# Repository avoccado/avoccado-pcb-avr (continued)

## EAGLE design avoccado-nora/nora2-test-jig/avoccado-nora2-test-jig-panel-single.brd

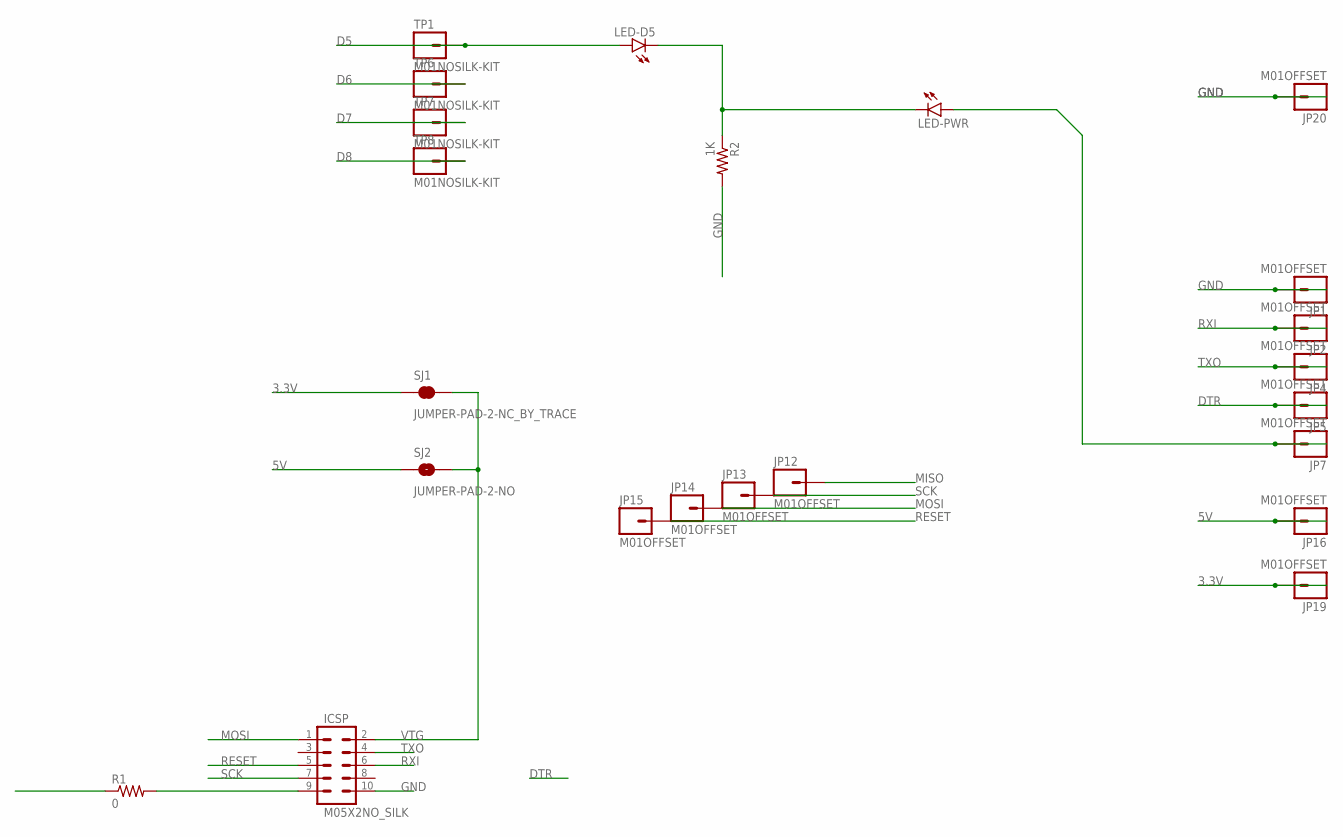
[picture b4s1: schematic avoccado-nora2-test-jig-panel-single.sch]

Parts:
ICSP: M05X2NO_SILK; 2X5_NOSILK
JP1, JP2, JP4, JP5, JP7, JP12, JP13, JP14, JP15, JP16, JP19, JP20: M01OFFSET; 1X01_OFFSET
LED-D5: LED0603; LED-0603
LED-PWR: LED0603; LED-0603
R1: 0; 1206
R2: 1K; 0603-RES
SJ1: JUMPER-PAD-2-NC_BY_TRACE; PAD-JUMPER-2-NC_BY_TRACE_YES_SILK
SJ2: JUMPER-PAD-2-NO; PAD-JUMPER-2-NO_NO_SILK
TP1, TP6, TP7, TP8: M01NOSILK-KIT; 1X01NS-KIT

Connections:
3.3V: JP19.1, SJ1.1
5V: JP16.1, SJ2.1
D5: LED-D5.A, TP1.1
D6: TP6.1
D7: TP7.1
D8: TP8.1
DTR: JP5.1
GND: ICSP.10, JP1.1, JP20.1, R2.2
MISO: JP12.1, R1.1
MISO1: ICSP.9, R1.2
MOSI: ICSP.1, JP14.1
unnamed: LED-D5.C, LED-PWR.C, R2.1
unnamed: JP7.1, LED-PWR.A
RESET: ICSP.5, JP15.1
RXI: ICSP.6, JP2.1
SCK: ICSP.7, JP13.1
TXO: ICSP.4, JP4.1
VTG: ICSP.2, SJ1.2, SJ2.2

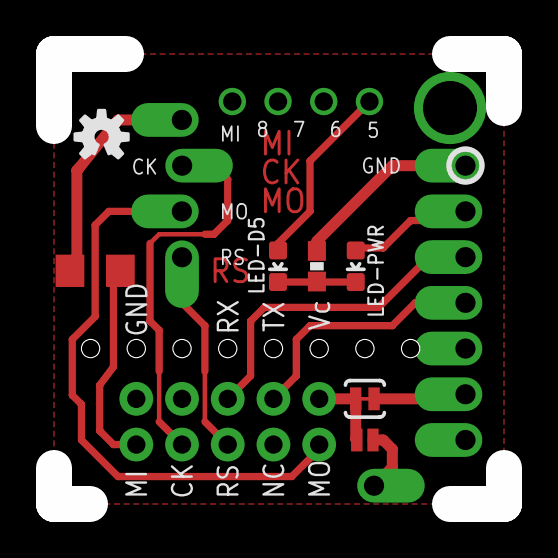
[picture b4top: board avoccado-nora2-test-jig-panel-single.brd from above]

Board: 2 copper layers, 25.0 x 25.0 mm, 24 parts (1 on the bottom side), 14 nets.

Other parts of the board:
LOGO2: OSHW-LOGOS; OSHW-LOGO-S

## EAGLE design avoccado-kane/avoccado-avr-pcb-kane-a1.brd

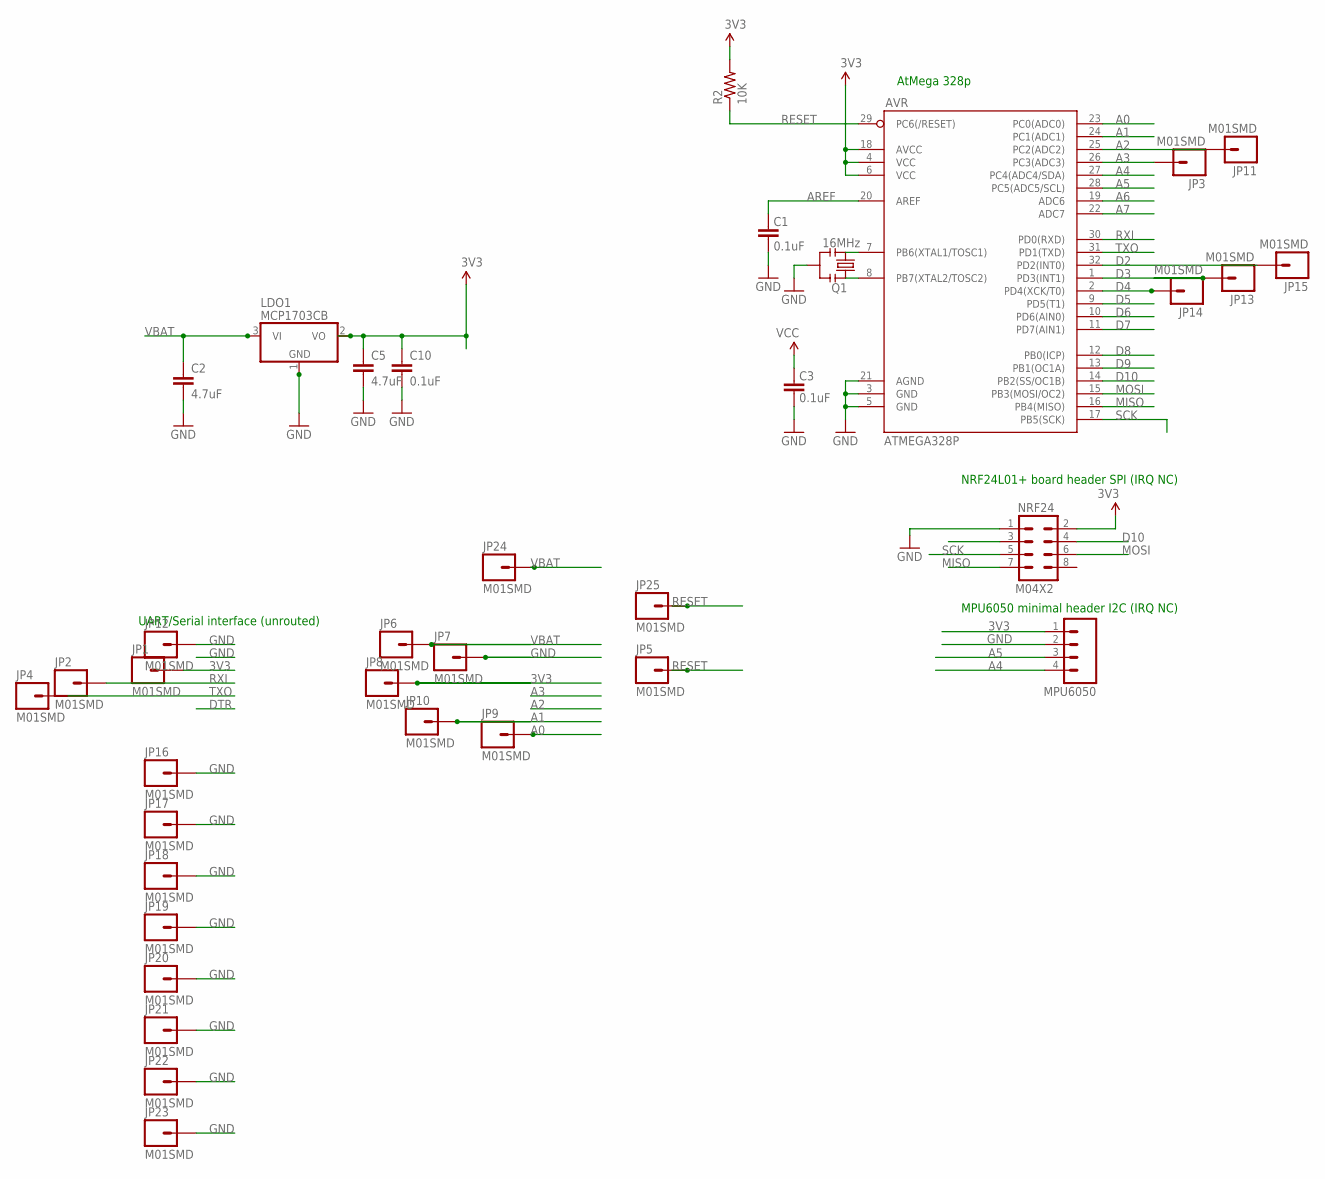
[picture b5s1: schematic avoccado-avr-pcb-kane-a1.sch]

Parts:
AVR: ATMEGA328P; TQFP32-08
C1, C3, C10: 0.1uF; C0402
C2, C5: 4.7uF; 0603-CAP
JP1, JP2, JP3, JP4, JP5, JP6, JP7, JP8, JP9, JP10, JP11, JP12, JP13, JP14, JP15, JP16, JP17, JP18, JP19, JP20, JP21, JP22, JP23, JP24, JP25: M01SMD; LUXEON-PAD
LDO1: MCP1703CB; SOT23
MPU6050: M041X04_NO_SILK; 1X04_NO_SILK
NRF24: M04X2; 2X4
Q1: 16MHz; RESONATOR-SMD
R2: 10K; 0603-RES

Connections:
3V3: AVR.4 (VCC), AVR.6 (VCC), AVR.18 (AVCC), C3.2, C5.1, C10.1, JP1.P$1, JP8.P$1, LDO1.2 (VO), MPU6050.1, NRF24.2, R2.2
A0: AVR.23 (PC0(ADC0)), JP9.P$1
A1: AVR.24 (PC1(ADC1)), JP10.P$1
A2: AVR.25 (PC2(ADC2)), JP11.P$1
A3: AVR.26 (PC3(ADC3)), JP3.P$1
A4: AVR.27 (PC4(ADC4/SDA)), MPU6050.4
A5: AVR.28 (PC5(ADC5/SCL)), MPU6050.3
A6: AVR.19 (ADC6)
A7: AVR.22 (ADC7)
AREF: AVR.20 (AREF), C1.2
D2: AVR.32 (PD2(INT0)), JP15.P$1
D3: AVR.1 (PD3(INT1)), JP13.P$1
D4: AVR.2 (PD4(XCK/T0)), JP14.P$1
D5: AVR.9 (PD5(T1))
D6: AVR.10 (PD6(AIN0))
D7: AVR.11 (PD7(AIN1))
D8: AVR.12 (PB0(ICP))
D9: AVR.13 (PB1(OC1A)), NRF24.3
D10: AVR.14 (PB2(SS/OC1B)), NRF24.4
GND: AVR.3 (GND), AVR.5 (GND), AVR.21 (AGND), C1.1, C2.2, C3.1, C5.2, C10.2, JP7.P$1, JP12.P$1, JP16.P$1, JP17.P$1, JP18.P$1, JP19.P$1, JP20.P$1, JP21.P$1, JP22.P$1, JP23.P$1, LDO1.1 (GND), MPU6050.2, NRF24.1, Q1.2
MISO: AVR.16 (PB4(MISO)), NRF24.7
MOSI: AVR.15 (PB3(MOSI/OC2)), NRF24.6
unnamed: AVR.8 (PB7(XTAL2/TOSC2)), Q1.1
unnamed: AVR.7 (PB6(XTAL1/TOSC1)), Q1.3
RESET: AVR.29 (PC6(/RESET)), JP5.P$1, JP25.P$1, R2.1
RXI: AVR.30 (PD0(RXD)), JP2.P$1
SCK: AVR.17 (PB5(SCK)), NRF24.5
TXO: AVR.31 (PD1(TXD)), JP4.P$1
VBAT: C2.1, JP6.P$1, JP24.P$1, LDO1.3 (VI)

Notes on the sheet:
NRF24L01+ board header SPI (IRQ NC)
MPU6050 minimal header I2C (IRQ NC)
AtMega 328p
UART/Serial interface (unrouted)

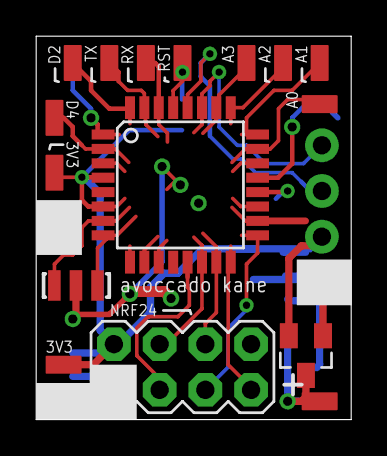
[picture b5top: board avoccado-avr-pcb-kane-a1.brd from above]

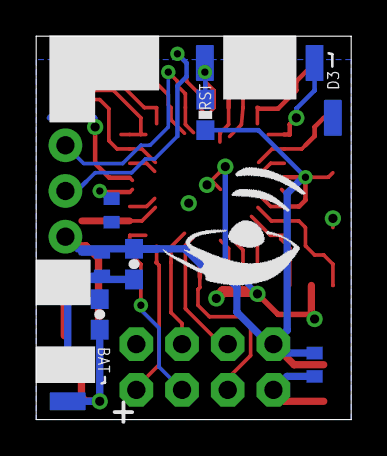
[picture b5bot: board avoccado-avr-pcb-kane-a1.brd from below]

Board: 2 copper layers, 17.5 x 21.3 mm, 36 parts (17 on the bottom side), 23 nets.

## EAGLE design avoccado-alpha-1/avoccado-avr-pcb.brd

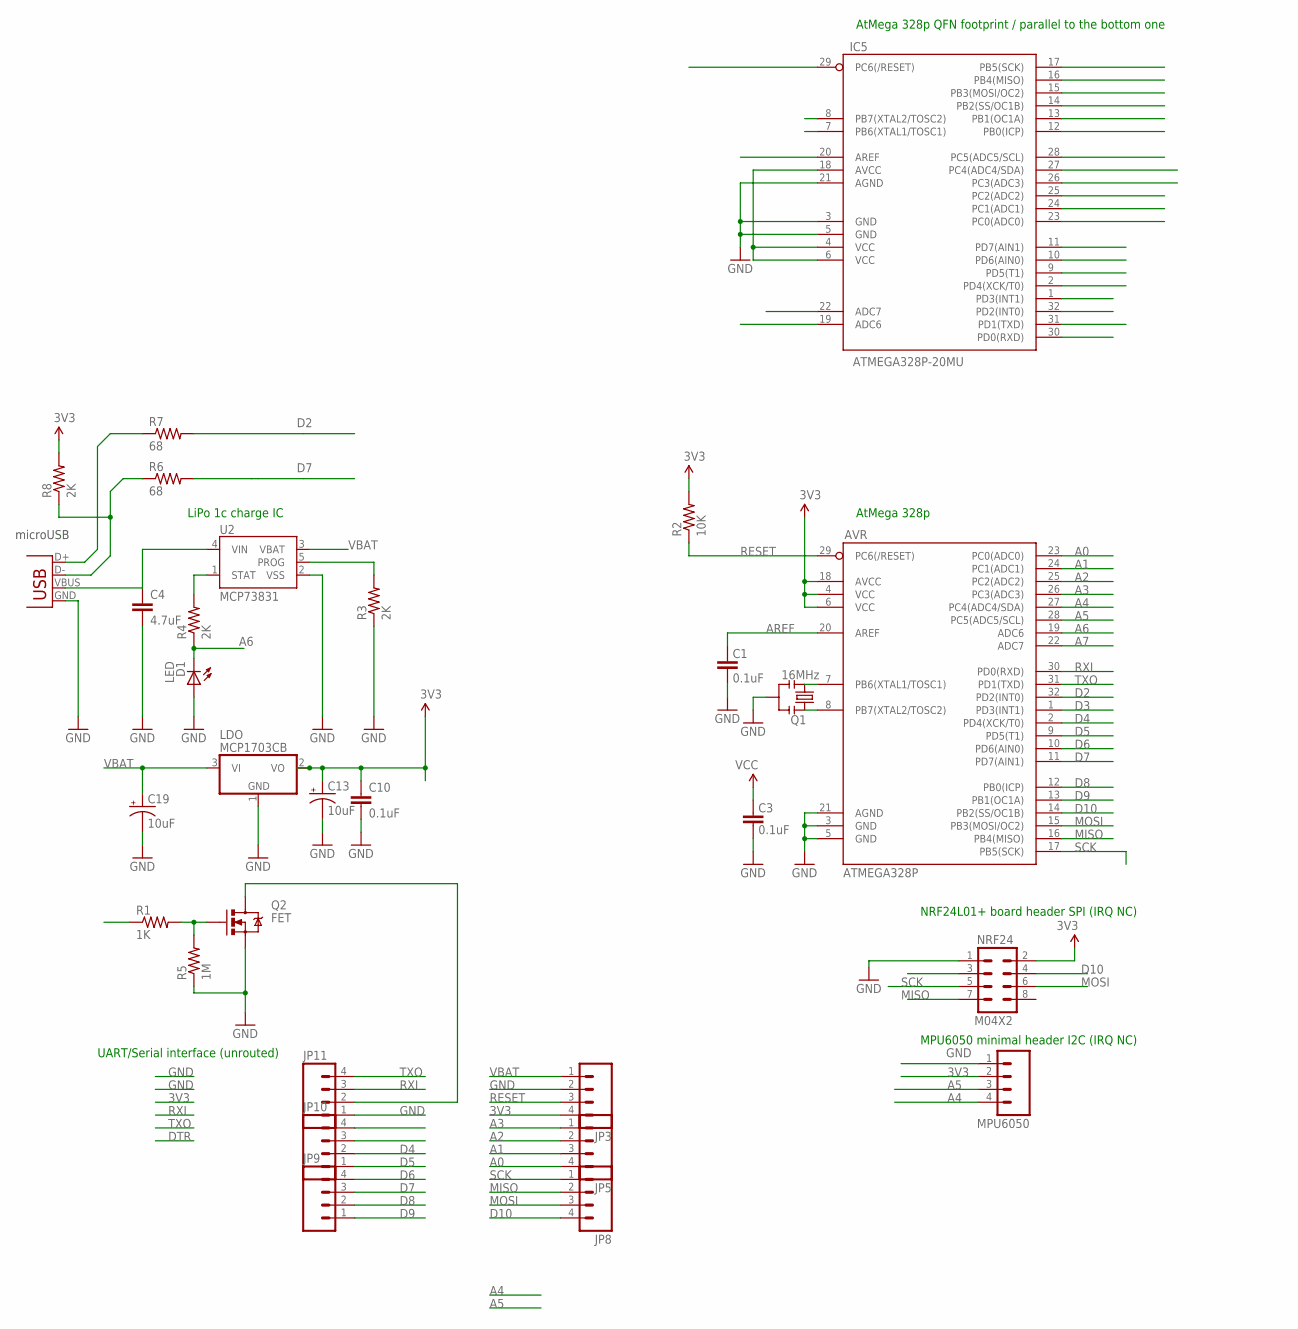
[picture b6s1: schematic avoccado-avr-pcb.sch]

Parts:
AVR: ATMEGA328P; TQFP32-08
C1, C3, C10: 0.1uF; C0402
C4: 4.7uF; 0603-CAP
C13, C19: 10uF; EIA3216
D1: LED; LED-0603
IC5: ATMEGA328P-20MU; MLF32
JP3, JP5, JP8, JP9, JP10, JP11: M04SMD1X4; 1X04-SMD
LDO: MCP1703CB; SOT23
MPU6050: M041X04_NO_SILK; 1X04_NO_SILK
NRF24: M04X2; 2X4
Q1: 16MHz; RESONATOR-SMD
Q2: FET; SOT323
R1: 1K; 0603-RES
R2: 10K; 0603-RES
R3, R4, R8: 2K; 0603-RES
R5: 1M; 0603-RES
R6, R7: 68; 0603-RES
U2: MCP73831; SOT23-5
X1: Micro USB; USB-MICROB

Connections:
3V3: AVR.4 (VCC), AVR.6 (VCC), AVR.18 (AVCC), C3.2, C10.1, C13.A (+), IC5.4 (VCC), IC5.6 (VCC), IC5.18 (AVCC), JP3.4, LDO.2 (VO), MPU6050.2, NRF24.2, R2.2, R8.2
A0: AVR.23 (PC0(ADC0)), IC5.23 (PC0(ADC0)), JP5.4
A1: AVR.24 (PC1(ADC1)), IC5.24 (PC1(ADC1)), JP5.3
A2: AVR.25 (PC2(ADC2)), IC5.25 (PC2(ADC2)), JP5.2
A3: AVR.26 (PC3(ADC3)), IC5.26 (PC3(ADC3)), JP5.1
A4: AVR.27 (PC4(ADC4/SDA)), IC5.27 (PC4(ADC4/SDA)), MPU6050.4
A5: AVR.28 (PC5(ADC5/SCL)), IC5.28 (PC5(ADC5/SCL)), MPU6050.3
A6: AVR.19 (ADC6), D1.C, IC5.19 (ADC6), R4.1
A7: AVR.22 (ADC7), IC5.22 (ADC7)
AREF: AVR.20 (AREF), C1.2, IC5.20 (AREF)
BUS: C4.1, U2.4 (VIN), X1.VBUS
D2: AVR.32 (PD2(INT0)), IC5.32 (PD2(INT0)), R7.2
D3: AVR.1 (PD3(INT1)), IC5.1 (PD3(INT1)), R1.1
D4: AVR.2 (PD4(XCK/T0)), IC5.2 (PD4(XCK/T0)), JP10.2
D5: AVR.9 (PD5(T1)), IC5.9 (PD5(T1)), JP10.1
D6: AVR.10 (PD6(AIN0)), IC5.10 (PD6(AIN0)), JP9.4
D7: AVR.11 (PD7(AIN1)), IC5.11 (PD7(AIN1)), JP9.3, R6.2
D8: AVR.12 (PB0(ICP)), IC5.12 (PB0(ICP)), JP9.2
D9: AVR.13 (PB1(OC1A)), IC5.13 (PB1(OC1A)), JP9.1, NRF24.3
D10: AVR.14 (PB2(SS/OC1B)), IC5.14 (PB2(SS/OC1B)), JP8.4, NRF24.4
GND: AVR.3 (GND), AVR.5 (GND), AVR.21 (AGND), C1.1, C3.1, C4.2, C10.2, C13.C (-), C19.C (-), D1.A, IC5.3 (GND), IC5.5 (GND), IC5.21 (AGND), JP3.2, JP10.3, JP10.4, JP11.1, LDO.1 (GND), MPU6050.1, NRF24.1, Q1.2, Q2.2 (S), R3.1, R5.1, U2.2 (VSS), X1.GND
MISO: AVR.16 (PB4(MISO)), IC5.16 (PB4(MISO)), JP8.2, NRF24.7
MOSI: AVR.15 (PB3(MOSI/OC2)), IC5.15 (PB3(MOSI/OC2)), JP8.3, NRF24.6
unnamed: AVR.8 (PB7(XTAL2/TOSC2)), IC5.8 (PB7(XTAL2/TOSC2)), Q1.1
unnamed: AVR.7 (PB6(XTAL1/TOSC1)), IC5.7 (PB6(XTAL1/TOSC1)), Q1.3
unnamed: R3.2, U2.5 (PROG)
unnamed: R4.2, U2.1 (STAT)
unnamed: Q2.1 (G), R1.2, R5.2
RESET: AVR.29 (PC6(/RESET)), IC5.29 (PC6(/RESET)), JP3.3, R2.1
RXI: AVR.30 (PD0(RXD)), IC5.30 (PD0(RXD)), JP11.3
SCK: AVR.17 (PB5(SCK)), IC5.17 (PB5(SCK)), JP8.1, NRF24.5
TXO: AVR.31 (PD1(TXD)), IC5.31 (PD1(TXD)), JP11.4
USB-D+: R7.1, X1.D+
USB-D-: R6.1, R8.1, X1.D-
VBAT: C19.A (+), JP3.1, LDO.3 (VI), U2.3 (VBAT)
VIBR: JP11.2, Q2.3 (D)

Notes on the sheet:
microUSB
NRF24L01+ board header SPI (IRQ NC)
MPU6050 minimal header I2C (IRQ NC)
AtMega 328p
AtMega 328p QFN footprint / parallel to the bottom one
LiPo 1c charge IC
UART/Serial interface (unrouted)

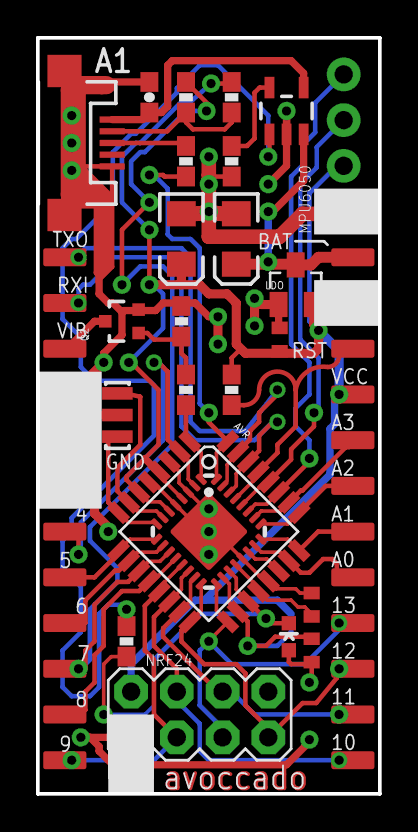
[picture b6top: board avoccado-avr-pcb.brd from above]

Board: 2 copper layers, 19.0 x 42.0 mm, 30 parts (0 on the bottom side), 36 nets.
